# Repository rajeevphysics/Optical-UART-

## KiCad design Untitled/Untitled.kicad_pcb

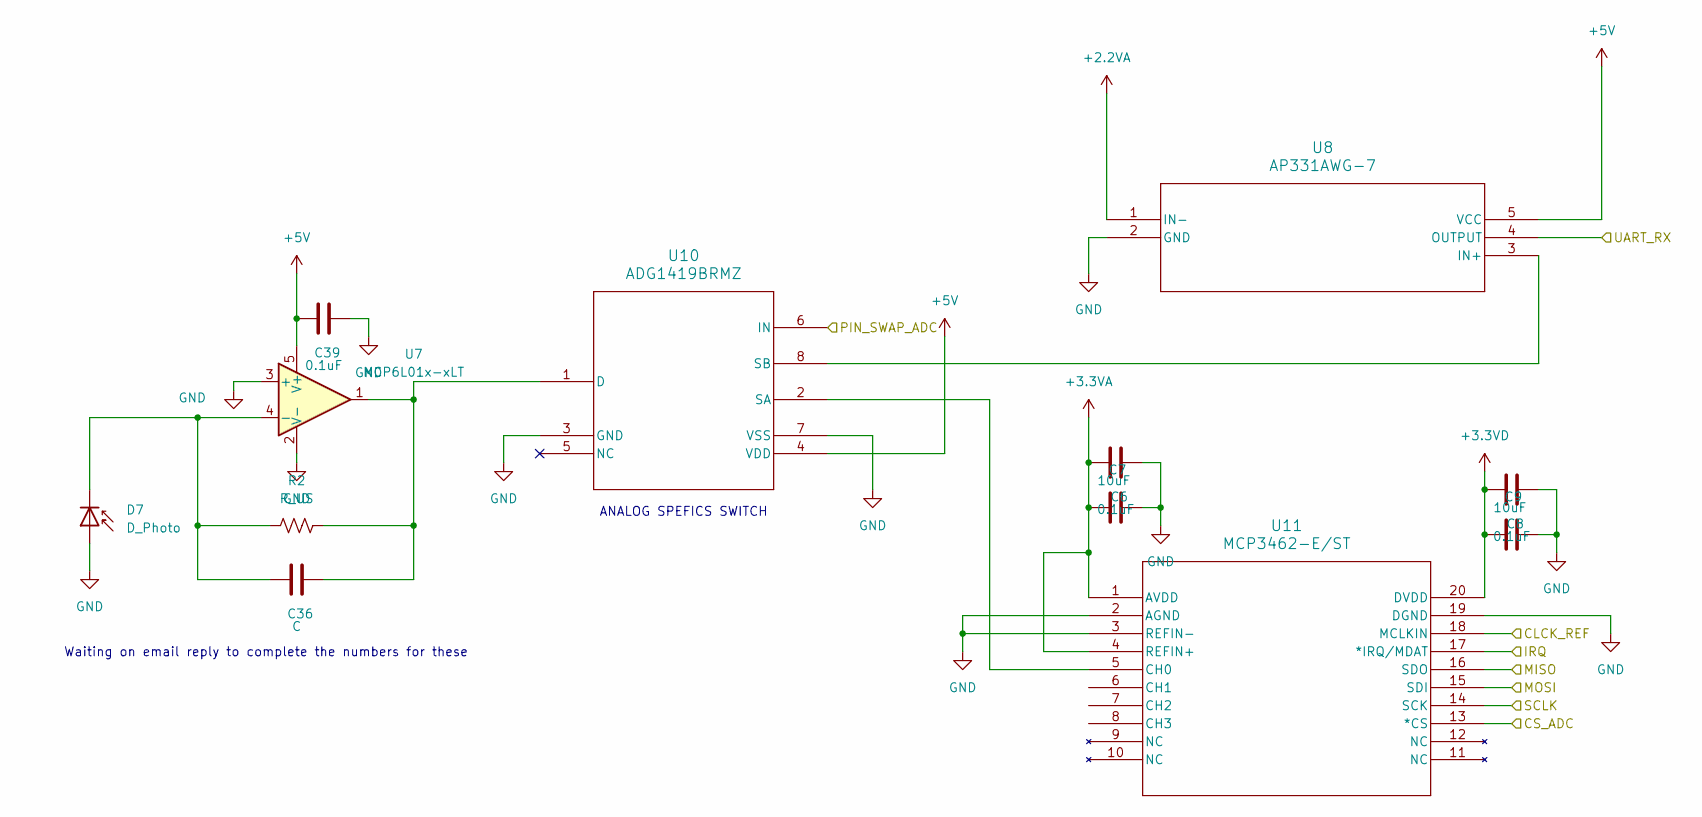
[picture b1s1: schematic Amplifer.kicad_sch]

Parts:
C6, C8, C39: 0.1uF; C_0805_2012Metric_Pad1.18x1.45mm_HandSolder
C7, C9: 10uF; C_0805_2012Metric_Pad1.18x1.45mm_HandSolder
C36: C; C_0805_2012Metric_Pad1.18x1.45mm_HandSolder
D7: D_Photo; TO99_BPW20RF_VIS
R2: R_US; R_0805_2012Metric_Pad1.20x1.40mm_HandSolder
U7: MCP6L01x-xLT; SOT-353_SC-70-5
U8: AP331AWG-7; SOT25_DIO
U10: ADG1419BRMZ; RM_8_ADI
U11: MCP3462-E/ST; TSSOP20_ST_MCH_MIS

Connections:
+2.2VA: U8.1 (IN-); also elsewhere on the board
+3.3VA: C6.1, C7.1, U11.1 (AVDD), U11.4 (REFIN+); also elsewhere on the board
+3.3VD: C8.1, C9.1, U11.20 (DVDD); also elsewhere on the board
+5V: C39.1, U7.5 (V+), U8.5 (VCC), U10.4 (VDD); also elsewhere on the board
/Analog Amplifer/UART_RX: U8.4 (OUTPUT); also elsewhere on the board
/CS_ADC: U11.13 (*CS); also elsewhere on the board
/IRQ: U11.17 (*IRQ/MDAT); also elsewhere on the board
/MISO: U11.16 (SDO); also elsewhere on the board
/MOSI: U11.15 (SDI); also elsewhere on the board
/PIN_SWAP_ADC: U10.6 (IN); also elsewhere on the board
/REF_CLK: U11.18 (MCLKIN); also elsewhere on the board
/SCLK: U11.14 (SCK); also elsewhere on the board
GND: C6.2, C7.2, C8.2, C9.2, C39.2, D7.2 (A), U7.2 (V-), U7.3 (+), U8.2 (GND), U10.3 (GND), U10.7 (VSS), U11.2 (AGND), U11.3 (REFIN-), U11.19 (DGND); also elsewhere on the board
unnamed: C36.1, D7.1 (K), R2.1, U7.4 (-)
unnamed: C36.2, R2.2, U7.1, U10.1 (D)
unnamed: U10.2 (SA), U11.5 (CH0)
unnamed: U8.3 (IN+), U10.8 (SB)

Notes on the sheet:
ANALOG SPEFICS SWITCH
Waiting on email reply to complete the numbers for these

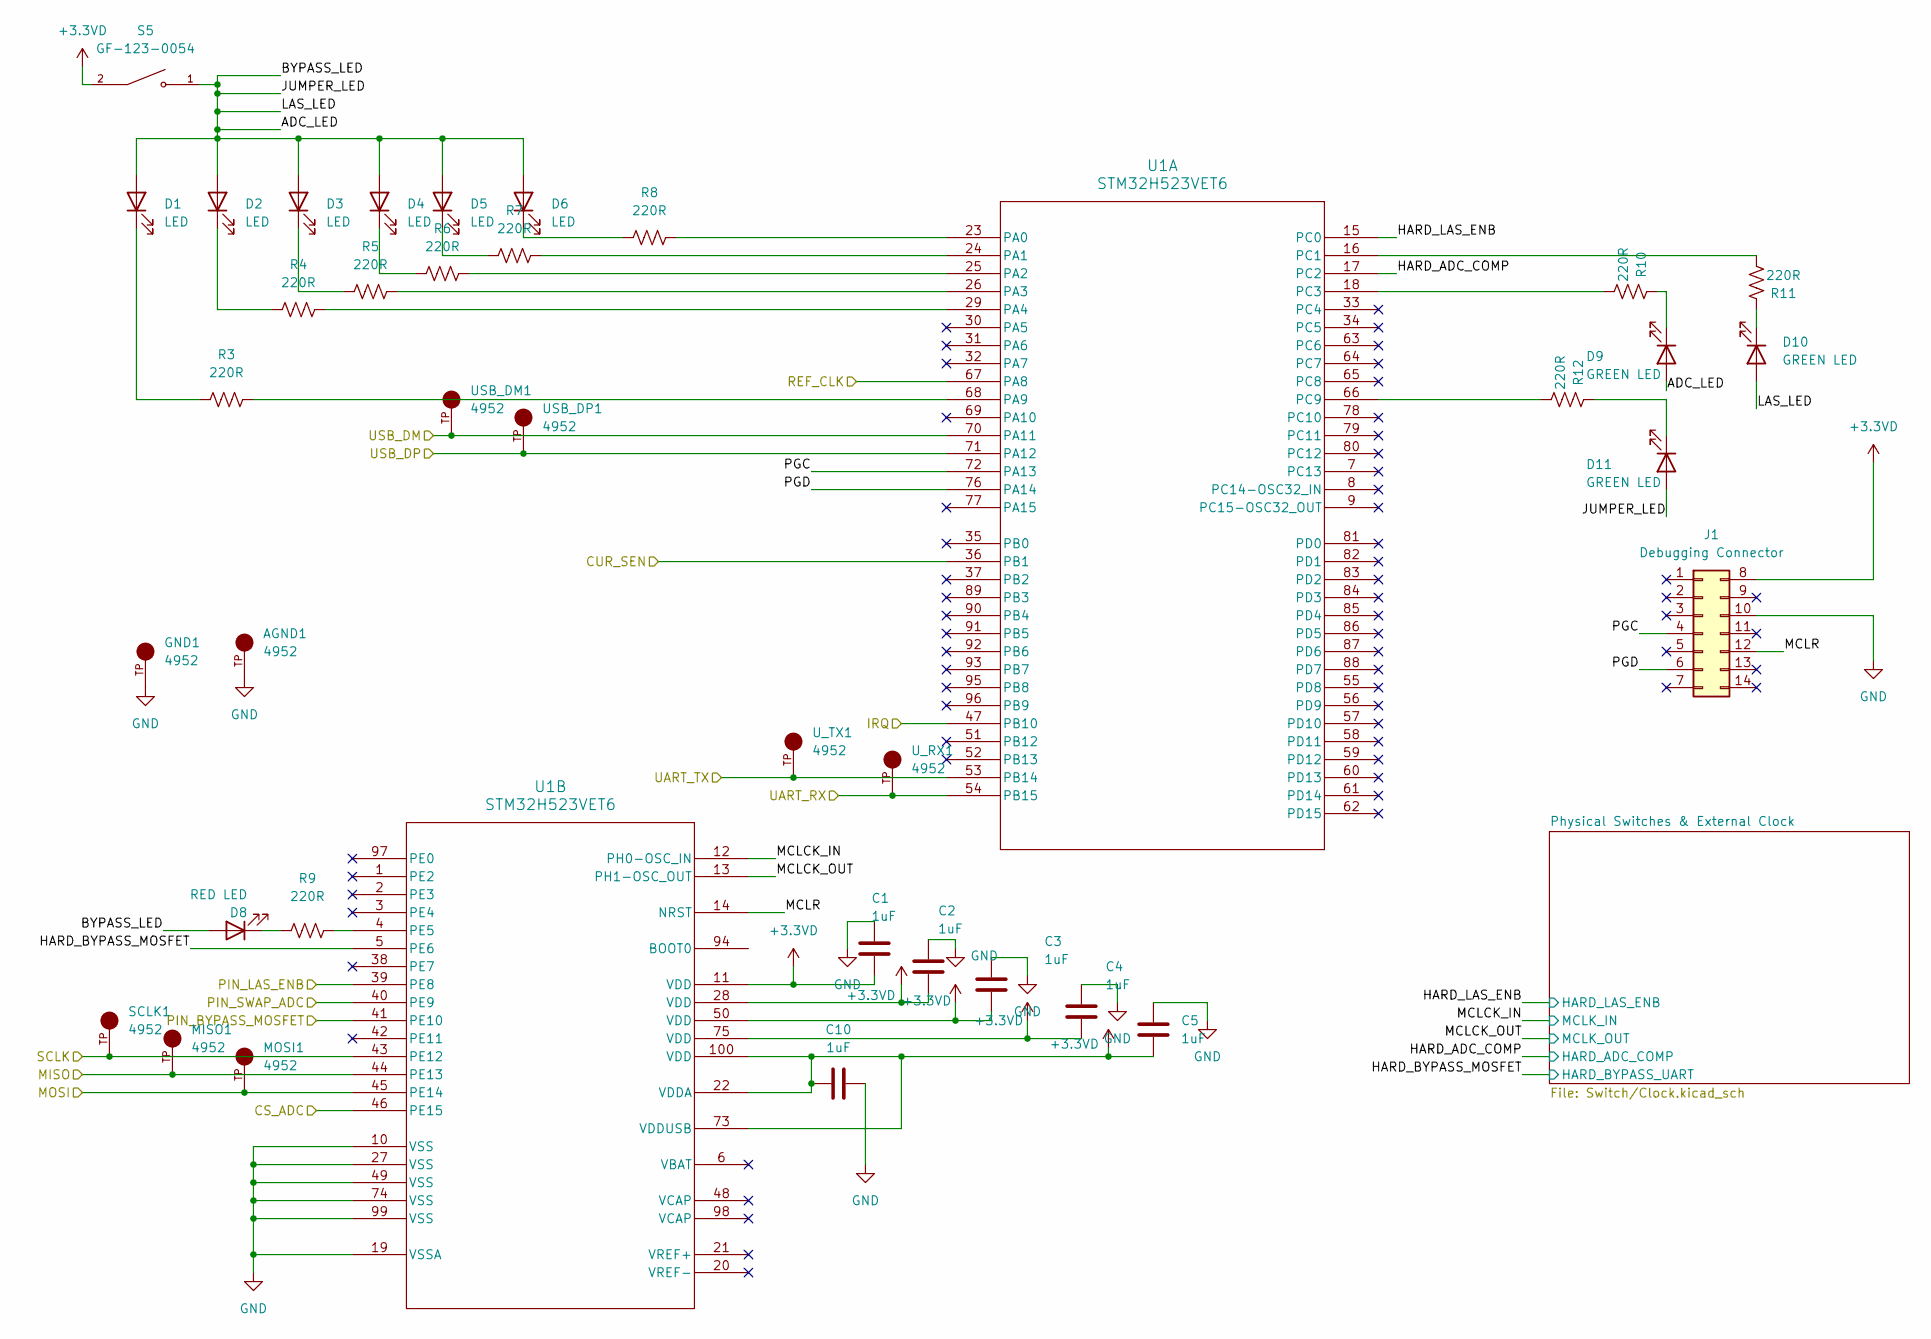
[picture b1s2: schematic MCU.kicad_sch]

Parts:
AGND1: 4952; KEYSTONE_4952; PARTREV A
C1, C2, C3, C4, C5, C10: 1uF; C_0805_2012Metric_Pad1.18x1.45mm_HandSolder
D1, D2, D3, D4, D5, D6: LED; LED_1206_3216Metric_Pad1.42x1.75mm_HandSolder
D8: RED LED; LED_1206_3216Metric_Pad1.42x1.75mm_HandSolder
D9, D10, D11: GREEN LED; LED_1206_3216Metric_Pad1.42x1.75mm_HandSolder
GND1: 4952; KEYSTONE_4952; PARTREV A
J1: Debugging Connector; PinHeader_2x07_P1.27mm_Vertical_SMD
MISO1: 4952; KEYSTONE_4952; PARTREV A
MOSI1: 4952; KEYSTONE_4952; PARTREV A
R3, R4, R5, R6, R7, R8, R9, R10, R11, R12: 220R; R_0805_2012Metric_Pad1.20x1.40mm_HandSolder
S5: GF-123-0054; SW_GF-123-0054; PARTREV May 20, 2003
SCLK1: 4952; KEYSTONE_4952; PARTREV A
U1: STM32H523VET6; LQFP-100
USB_DM1: 4952; KEYSTONE_4952; PARTREV A
USB_DP1: 4952; KEYSTONE_4952; PARTREV A
U_RX1: 4952; KEYSTONE_4952; PARTREV A
U_TX1: 4952; KEYSTONE_4952; PARTREV A

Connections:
+3.3VD: C1.2, C2.1, C3.1, C4.1, C5.1, C10.2, J1.8, S5.2, U1.11 (VDD), U1.22 (VDDA), U1.28 (VDD), U1.50 (VDD), U1.73 (VDDUSB), U1.75 (VDD), U1.100 (VDD); also elsewhere on the board
/Analog Amplifer/UART_RX: U1.54 (PB15), U_RX1.TP; also elsewhere on the board
/CS_ADC: U1.46 (PE15); also elsewhere on the board
/IRQ: U1.47 (PB10); also elsewhere on the board
/Laser/UART_TX: U1.53 (PB14), U_TX1.TP; also elsewhere on the board
/MCU/ADC_LED: D1.2 (A), D2.2 (A), D3.2 (A), D4.2 (A), D5.2 (A), D6.2 (A), D8.2 (A), D9.2 (A), D10.2 (A), D11.2 (A), S5.1
/MCU/CUR_SEN: U1.36 (PB1); also elsewhere on the board
/MCU/HARD_ADC_COMP: U1.17 (PC2); also elsewhere on the board
/MCU/HARD_BYPASS_MOSFET: U1.5 (PE6); also elsewhere on the board
/MCU/HARD_LAS_ENB: U1.15 (PC0); also elsewhere on the board
/MCU/MCLCK_IN: U1.12 (PH0-OSC_IN); also elsewhere on the board
/MCU/MCLCK_OUT: U1.13 (PH1-OSC_OUT); also elsewhere on the board
/MCU/MCLR: J1.12, U1.14 (NRST)
/MCU/PGC: J1.4, U1.72 (PA13)
/MCU/PGD: J1.6, U1.76 (PA14)
/MCU/USB_DM: U1.70 (PA11), USB_DM1.TP; also elsewhere on the board
/MCU/USB_DP: U1.71 (PA12), USB_DP1.TP; also elsewhere on the board
/MISO: MISO1.TP, U1.44 (PE13); also elsewhere on the board
/MOSI: MOSI1.TP, U1.45 (PE14); also elsewhere on the board
/PIN_BYPASS_MOSFET: U1.41 (PE10); also elsewhere on the board
/PIN_LAS_ENB: U1.39 (PE8); also elsewhere on the board
/PIN_SWAP_ADC: U1.40 (PE9); also elsewhere on the board
/REF_CLK: U1.67 (PA8); also elsewhere on the board
/SCLK: SCLK1.TP, U1.43 (PE12); also elsewhere on the board
GND: AGND1.TP, C1.1, C2.2, C3.2, C4.2, C5.2, C10.1, GND1.TP, J1.10, U1.10 (VSS), U1.19 (VSSA), U1.27 (VSS), U1.49 (VSS), U1.74 (VSS), U1.99 (VSS); also elsewhere on the board
unnamed: D1.1 (K), R3.1
unnamed: D2.1 (K), R4.1
unnamed: D3.1 (K), R5.1
unnamed: D4.1 (K), R6.1
unnamed: D5.1 (K), R7.1
unnamed: D6.1 (K), R8.1
unnamed: D8.1 (K), R9.1
unnamed: D9.1 (K), R10.1
unnamed: D10.1 (K), R11.1
unnamed: D11.1 (K), R12.1
unnamed: R8.2, U1.23 (PA0)
unnamed: R7.2, U1.24 (PA1)
unnamed: R6.2, U1.25 (PA2)
unnamed: R5.2, U1.26 (PA3)
unnamed: R4.2, U1.29 (PA4)
unnamed: R3.2, U1.68 (PA9)
unnamed: R11.2, U1.16 (PC1)
unnamed: R10.2, U1.18 (PC3)
unnamed: R12.2, U1.66 (PC9)
unnamed: R9.2, U1.4 (PE5)

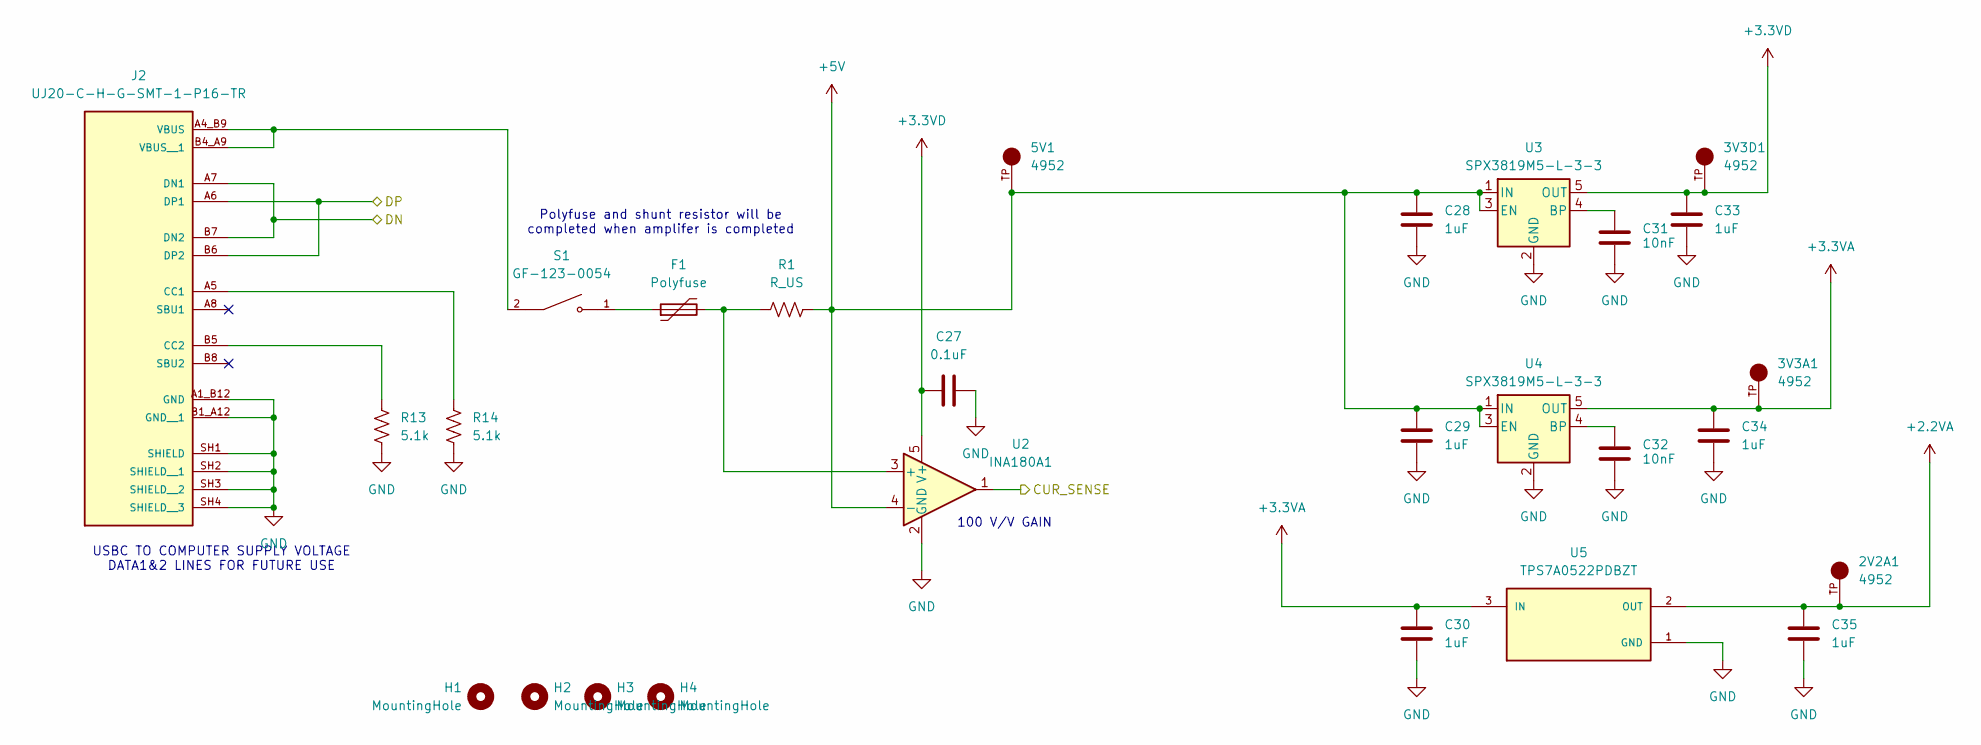
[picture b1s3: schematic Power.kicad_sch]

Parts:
2V2A1, 3V3A1, 3V3D1, 5V1: 4952; KEYSTONE_4952; PARTREV A
C27: 0.1uF; C_0805_2012Metric_Pad1.18x1.45mm_HandSolder
C28, C29, C30, C33, C34, C35: 1uF; C_0805_2012Metric_Pad1.18x1.45mm_HandSolder
C31, C32: 10nF; C_0805_2012Metric_Pad1.18x1.45mm_HandSolder
F1: Polyfuse; C_0805_2012Metric_Pad1.18x1.45mm_HandSolder
H1, H2, H3, H4: MountingHole; MountingHole_3.2mm_M3_ISO7380_Pad_TopBottom
J2: UJ20-C-H-G-SMT-1-P16-TR; SAMESKY_UJ20-C-H-G-SMT-1-P16-TR; PARTREV 1.0
R1: R_US; R_0805_2012Metric_Pad1.20x1.40mm_HandSolder
R13, R14: 5.1k; R_0805_2012Metric_Pad1.20x1.40mm_HandSolder
S1: GF-123-0054; SW_GF-123-0054; PARTREV May 20, 2003
U2: INA180A1; SOT-23-5
U3, U4: SPX3819M5-L-3-3; SOT-23-5
U5: TPS7A0522PDBZT; SOT-23TO-236_318-08_ONS; PARTREV D

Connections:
+2.2VA: 2V2A1.TP, C35.1, U5.2 (OUT); also elsewhere on the board
+3.3VA: 3V3A1.TP, C30.1, C34.1, U4.5 (OUT), U5.3 (IN); also elsewhere on the board
+3.3VD: 3V3D1.TP, C27.1, C33.1, U2.5 (V+), U3.5 (OUT); also elsewhere on the board
+5V: 5V1.TP, C28.1, C29.1, R1.2, U2.4 (-), U3.1 (IN), U3.3 (EN), U4.1 (IN), U4.3 (EN); also elsewhere on the board
/MCU/CUR_SEN: U2.1; also elsewhere on the board
/MCU/USB_DM: J2.A7 (DN1), J2.B7 (DN2); also elsewhere on the board
/MCU/USB_DP: J2.A6 (DP1), J2.B6 (DP2); also elsewhere on the board
GND: C27.2, C28.2, C29.2, C30.2, C31.2, C32.2, C33.2, C34.2, C35.2, J2.A1_B12 (GND), J2.B1_A12 (GND__1), J2.SH1 (SHIELD), J2.SH2 (SHIELD__1), J2.SH3 (SHIELD__2), J2.SH4 (SHIELD__3), R13.2, R14.2, U2.2 (GND), U3.2 (GND), U4.2 (GND), U5.1 (GND); also elsewhere on the board
unnamed: F1.1, S1.1
unnamed: J2.A5 (CC1), R14.1
unnamed: J2.B5 (CC2), R13.1
unnamed: J2.A4_B9 (VBUS), J2.B4_A9 (VBUS__1), S1.2
unnamed: F1.2, R1.1, U2.3 (+)
unnamed: C31.1, U3.4 (BP)
unnamed: C32.1, U4.4 (BP)

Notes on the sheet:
100 V/V GAIN
Polyfuse and shunt resistor will be completed when amplifer is completed
USBC TO COMPUTER SUPPLY VOLTAGE DATA1&2 LINES FOR FUTURE USE

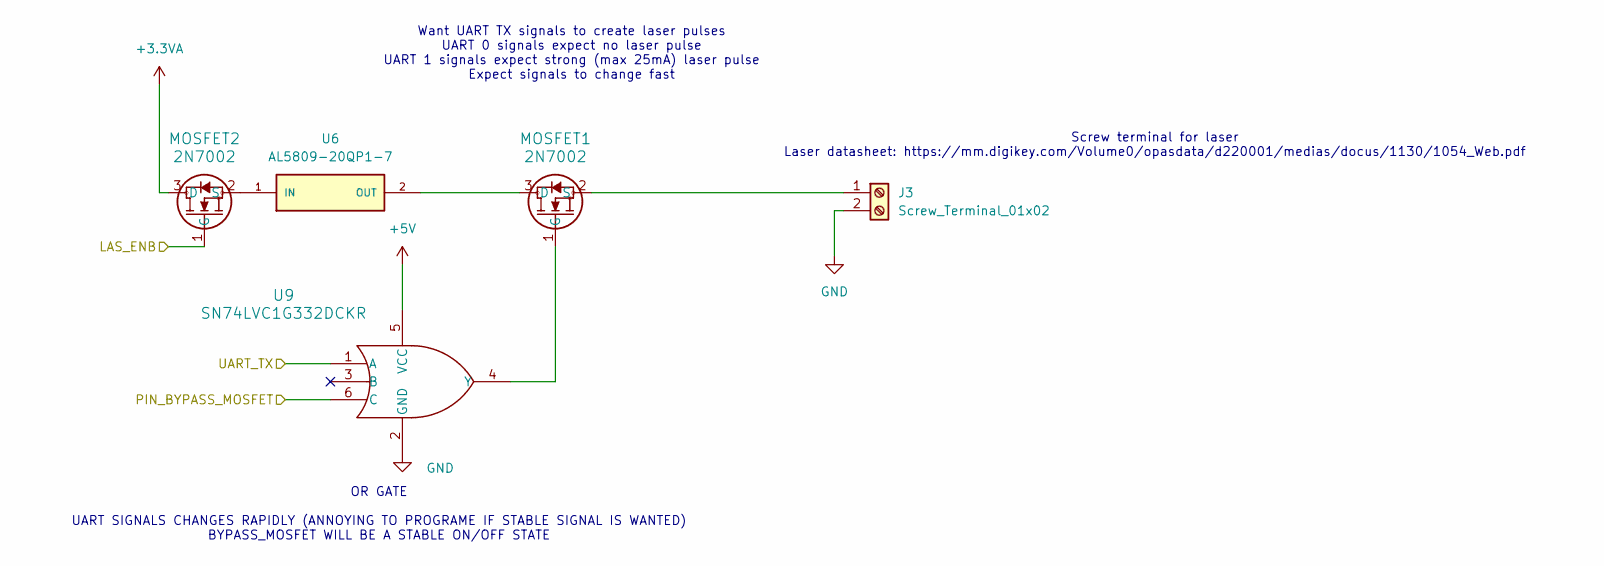
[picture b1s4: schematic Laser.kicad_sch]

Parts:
J3: Screw_Terminal_01x02; CONN_1729128_PXC
MOSFET1, MOSFET2: 2N7002; SOT-23TO-236_318-08_ONS
U6: AL5809-20QP1-7; SODFL3717X100N; PARTREV 2 - 2
U9: SN74LVC1G332DCKR; DCK0006A_N

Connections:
+3.3VA: MOSFET2.3 (D); also elsewhere on the board
+5V: U9.5 (VCC); also elsewhere on the board
/Laser/UART_TX: U9.1 (A); also elsewhere on the board
/PIN_BYPASS_MOSFET: U9.6 (C); also elsewhere on the board
/PIN_LAS_ENB: MOSFET2.1 (G); also elsewhere on the board
GND: J3.2, U9.2 (GND); also elsewhere on the board
unnamed: J3.1, MOSFET1.2 (S)
unnamed: MOSFET1.3 (D), U6.2 (OUT)
unnamed: MOSFET1.1 (G), U9.4 (Y)
unnamed: MOSFET2.2 (S), U6.1 (IN)

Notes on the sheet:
Want UART TX signals to create laser pulses UART 0 signals expect no laser pulse UART 1 signals expect strong (max 25mA) laser pulse Expect signals to change fast
Screw terminal for laser Laser datasheet: https://mm.digikey.com/Volume0/opasdata/d220001/medias/docus/1130/1054_Web.pdf
OR GATE UART SIGNALS CHANGES RAPIDLY (ANNOYING TO PROGRAME IF STABLE SIGNAL IS WANTED) BYPASS_MOSFET WILL BE A STABLE ON/OFF STATE

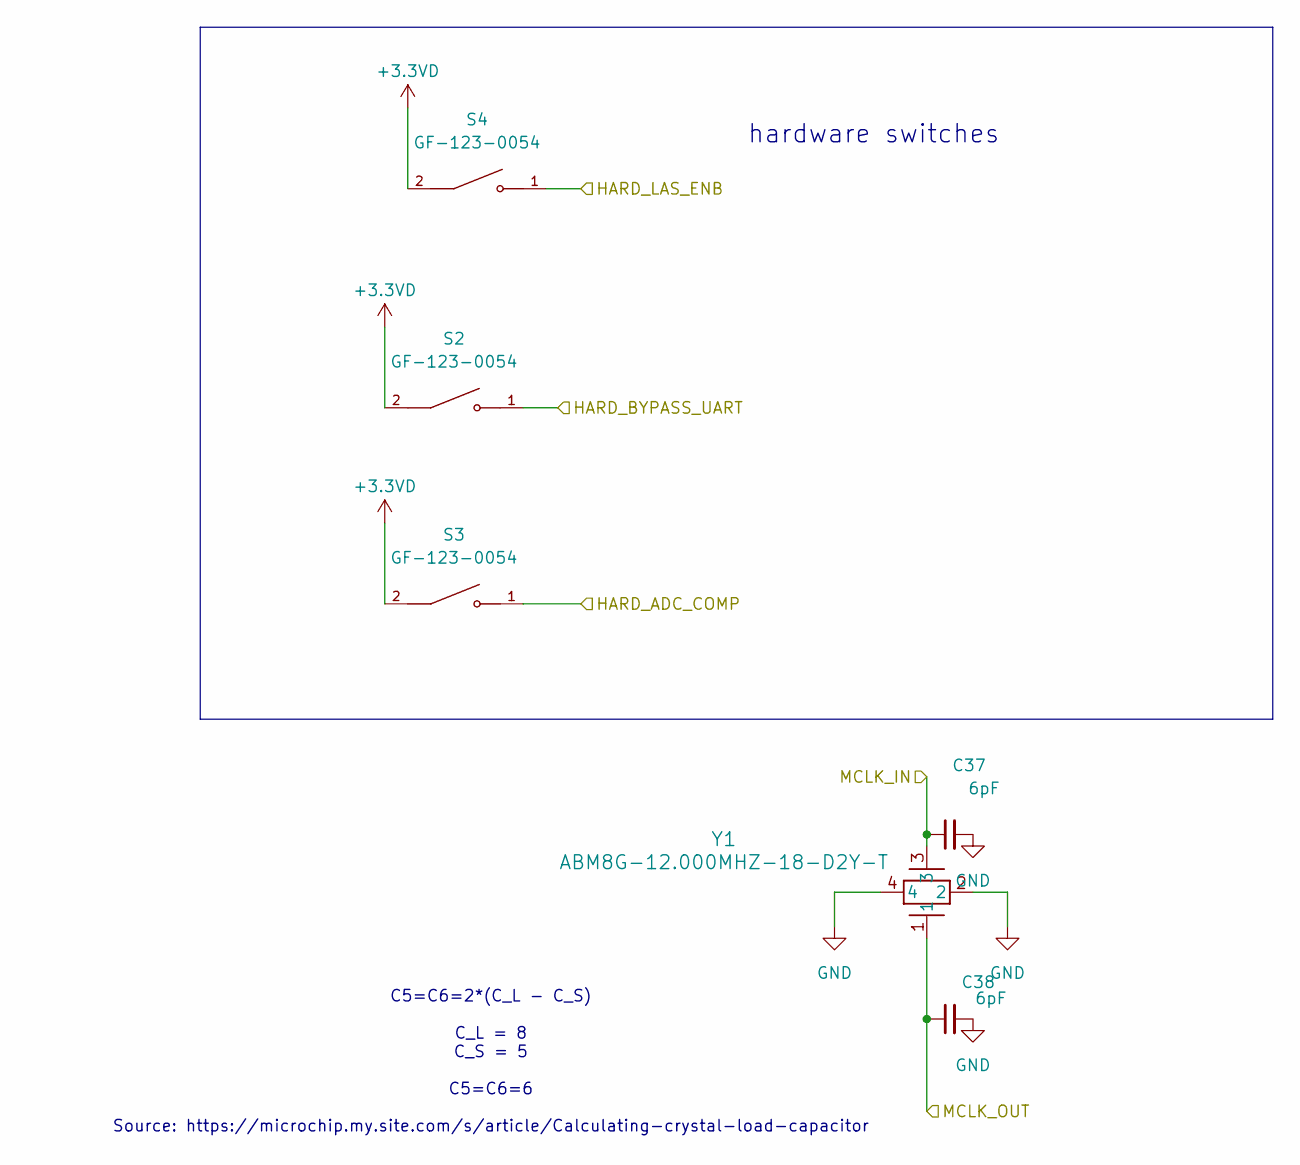
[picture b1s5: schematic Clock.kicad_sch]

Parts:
C37, C38: 6pF; C_0603_1608Metric_Pad1.08x0.95mm_HandSolder
S2, S3, S4: GF-123-0054; SW_GF-123-0054; PARTREV May 20, 2003
Y1: ABM8G-12.000MHZ-18-D2Y-T; CRYSTAL_ABM8G_ABR

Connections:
+3.3VD: S2.2, S3.2, S4.2; also elsewhere on the board
/MCU/HARD_ADC_COMP: S3.1; also elsewhere on the board
/MCU/HARD_BYPASS_MOSFET: S2.1; also elsewhere on the board
/MCU/HARD_LAS_ENB: S4.1; also elsewhere on the board
/MCU/MCLCK_IN: C37.1, Y1.3; also elsewhere on the board
/MCU/MCLCK_OUT: C38.1, Y1.1; also elsewhere on the board
GND: C37.2, C38.2, Y1.2, Y1.4; also elsewhere on the board

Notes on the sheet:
C5=C6=2*(C_L - C_S) C_L = 8 C_S = 5 C5=C6=6 Source: https://microchip.my.site.com/s/article/Calculating-crystal-load-capacitor
hardware switches

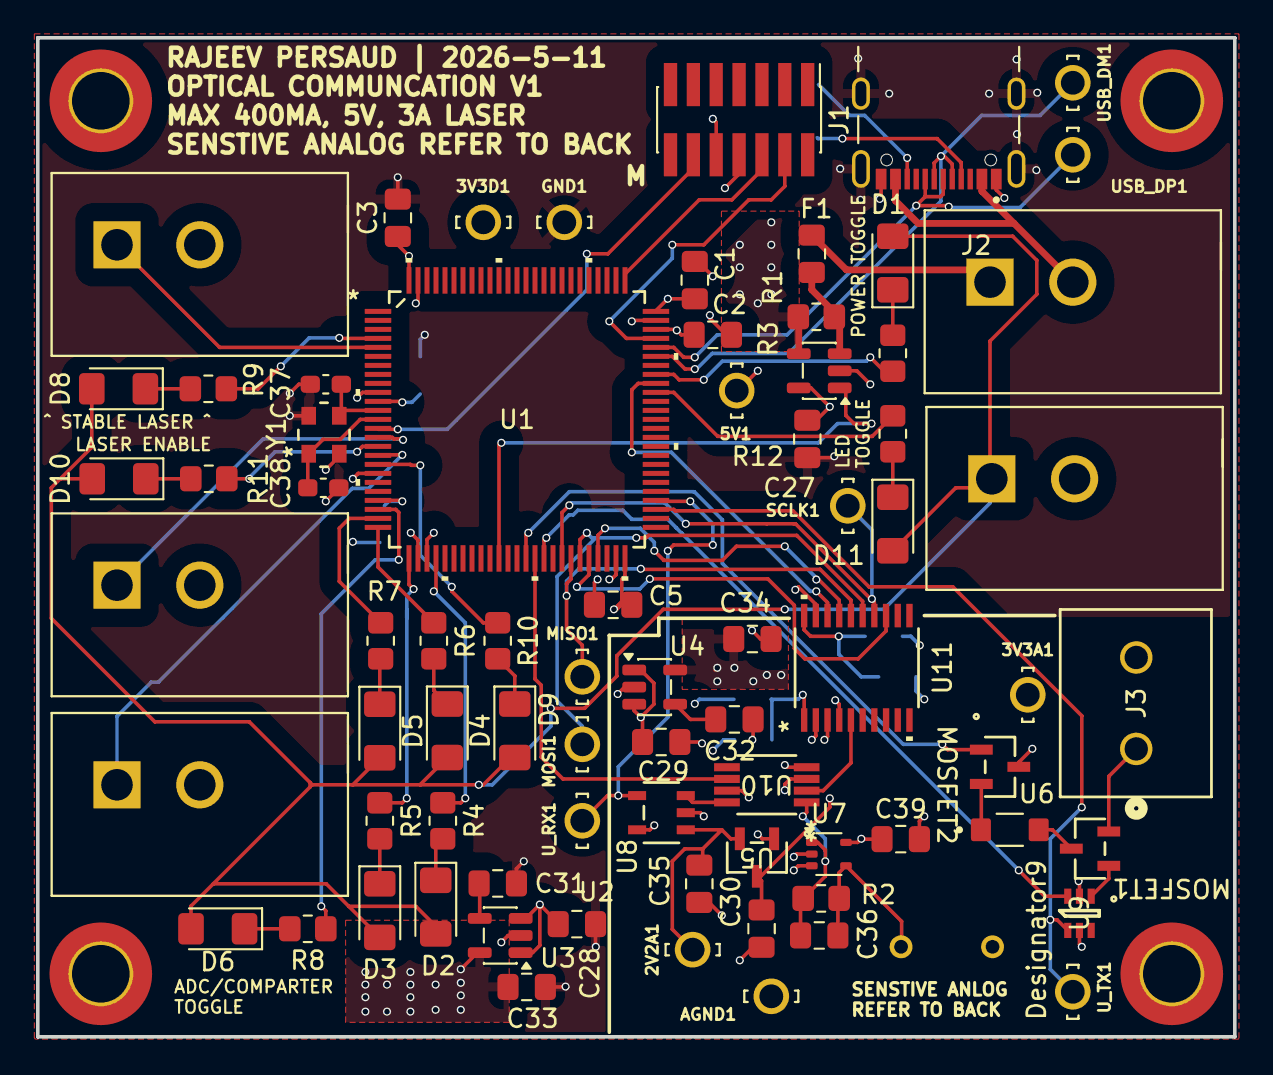
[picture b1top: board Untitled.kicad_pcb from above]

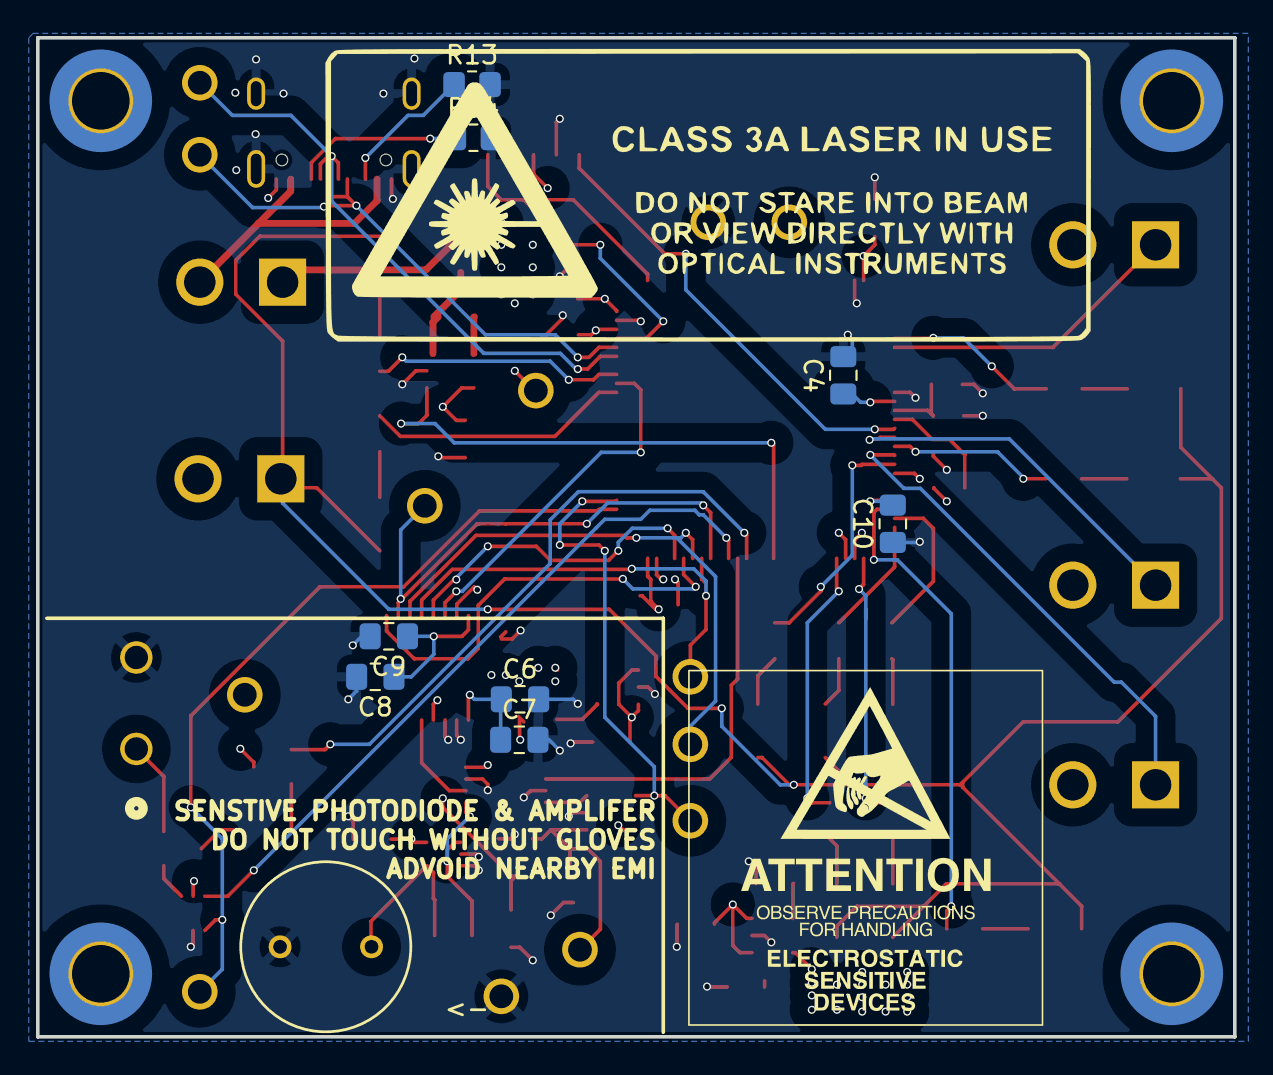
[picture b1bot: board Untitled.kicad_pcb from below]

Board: 4 copper layers, 66.5 x 55.5 mm, 88 parts (9 on the bottom side), 63 nets.

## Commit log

2026-05-05 Full schematic & PCB V1 of Optical Communcation for review
2026-05-05 Full changes
2026-05-07 revised verison
2026-05-07 schematic updates
2026-05-09 fixed board
2026-05-09 foorptint updates
